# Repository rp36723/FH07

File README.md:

# FH07

A Monorepo for ECE364D Senior Design, team FH07

This repo is maintained with the meson build system.

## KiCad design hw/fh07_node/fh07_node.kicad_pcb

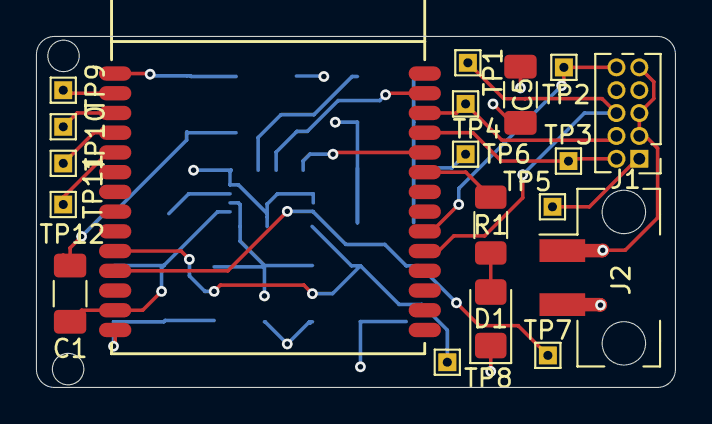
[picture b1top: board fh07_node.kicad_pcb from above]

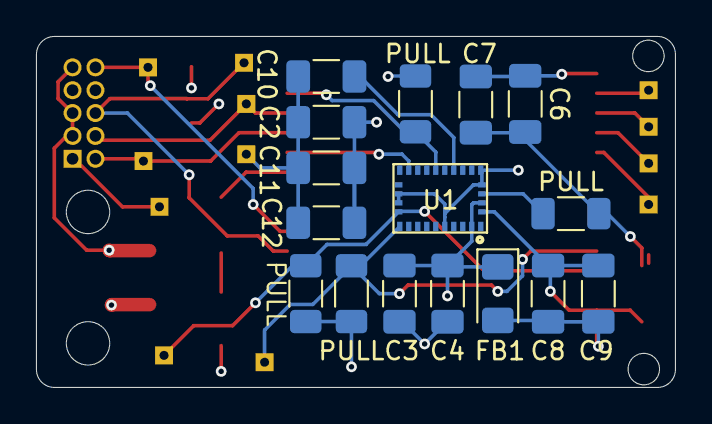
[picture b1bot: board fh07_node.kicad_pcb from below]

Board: 4 copper layers, 35.5 x 19.5 mm, 35 parts (16 on the bottom side), 19 nets.

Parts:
C1, C2, C3, C4, C5, C6, C7: C_Small; C_1206_3216Metric_Pad1.33x1.80mm_HandSolder
C8: 0.1 uF; C_1206_3216Metric_Pad1.33x1.80mm_HandSolder
C9: 4.7 uF; C_1206_3216Metric_Pad1.33x1.80mm_HandSolder
C10: 1 uF; C_1206_3216Metric_Pad1.33x1.80mm_HandSolder
C11: 120 nF; C_1206_3216Metric_Pad1.33x1.80mm_HandSolder
C12: 100 nF; C_1206_3216Metric_Pad1.33x1.80mm_HandSolder
D1: LED; D_1206_3216Metric_Pad1.42x1.75mm_HandSolder
FB1: FerriteBead; D_1206_3216Metric_Pad1.42x1.75mm_HandSolder
J1: Conn_ARM_JTAG_SWD_10; PinHeader_2x05_P1.27mm_Vertical
J2: Conn_01x02; Molex_Micro-Fit_3.0_43650-0221_1x02_P3.00mm_Vertical
M1: ME54BS01_V1.0
PULL: 4.7k; R_1206_3216Metric_Pad1.30x1.75mm_HandSolder
PULL#2, PULL#4: 10k; R_1206_3216Metric_Pad1.30x1.75mm_HandSolder
PULL#3: 4.7k; R_1206_3216Metric_Pad1.30x1.75mm_HandSolder
R1: 2.2 kΩ; R_1206_3216Metric_Pad1.30x1.75mm_HandSolder
TP1: TestPoint_SWO; TestPoint_THTPad_1.0x1.0mm_Drill0.5mm
TP2: TestPoint_nRESET; TestPoint_THTPad_1.0x1.0mm_Drill0.5mm
TP3: TestPoint_SWDIO; TestPoint_THTPad_1.0x1.0mm_Drill0.5mm
TP4: TestPoint_SWCLK; TestPoint_THTPad_1.0x1.0mm_Drill0.5mm
TP5: TestPoint_VCC; TestPoint_THTPad_1.0x1.0mm_Drill0.5mm
TP6: TestPoint_GND; TestPoint_THTPad_1.0x1.0mm_Drill0.5mm
TP7: TestPoint_SCL; TestPoint_THTPad_1.0x1.0mm_Drill0.5mm
TP8: TestPoint_SDA; TestPoint_THTPad_1.0x1.0mm_Drill0.5mm
TP9: TestPoint_1; TestPoint_THTPad_1.0x1.0mm_Drill0.5mm
TP10: TestPoint_2; TestPoint_THTPad_1.0x1.0mm_Drill0.5mm
TP11: TestPoint_3; TestPoint_THTPad_1.0x1.0mm_Drill0.5mm
TP12: TestPoint_4; TestPoint_THTPad_1.0x1.0mm_Drill0.5mm
U1: BNO055; LGA28R50P4X10_380X520X100

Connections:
+2V5: C1.1, C2.1, C3.1, C4.1, C5.1, C6.1, C7.1, C11.1, C12.1, FB1.1, J1.1 (VTref), J2.2, PULL.1, PULL#2.1, PULL#3.1, PULL#4.1, TP5.1, U1.3 (VDD), U1.28 (VDDIO)
/MCU/BNO_INT: M1.24 (P0.01), U1.14 (INT)
/MCU/BNO_nRESET: M1.27 (P0.02), PULL#2.2, U1.11 (NRESET)
/MCU/LED_STAT: M1.23 (P0.00), R1.1
/MCU/VCCM_nRF: C8.1, C9.1, FB1.2, M1.14 (VCCM_nRF)
/SCL: M1.11 (P1.03/NFC2), PULL#3.2, TP7.1, U1.19 (COM1)
/SDA: M1.10 (P1.02/NFC1), PULL.2, TP8.1, U1.20 (COM0)
/SWCLK: J1.4 (SWCLK/TCK), M1.26 (SWDCLK), TP4.1
/SWDIO: J1.2 (SWDIO/TMS), M1.25 (SWDIO), TP3.1
/SWO: J1.6 (SWO/TDO), M1.19 (P2.07), TP1.1
/Sensors/BNO_nBOOT_LOAD_PIN: PULL#4.2, U1.4 (NBOOT_LOAD_PIN)
/TP_1: M1.2 (P1.09), TP9.1
/TP_2: M1.3 (P1.10), TP10.1
/TP_3: M1.4 (P1.11/AIN4), TP11.1
/TP_4: M1.5 (P1.12/AIN5), TP12.1
/nRESET: J1.10 (~RESET), M1.20 (NRESET), TP2.1
GND: C1.2, C2.2, C3.2, C4.2, C5.2, C6.2, C7.2, C8.2, C9.2, C10.2, C11.2, C12.2, D1.1 (K), J1.3 (GND), J1.5 (GND), J1.9 (GNDDetect), J2.1, M1.1 (GND), M1.13 (GND), TP6.1, U1.2 (GND), U1.5 (PS1), U1.6 (PS0), U1.17 (COM3), U1.18 (COM2), U1.25 (GNDIO)
unnamed: D1.2 (A), R1.2
unnamed: C10.1, U1.9 (CAP)

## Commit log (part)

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2025-10-27 Basic init for messaging formats
2025-10-27 Added basic README
2025-10-27 Gitignore comments
2025-10-27 Added timestamp functionality
2025-10-27 Cleaned up build scripts and added flatbuffer dependency
2025-10-27 README updates
2025-11-13 risk reduction html page
2025-11-19 mockup for mobile app
2025-11-19 Add outlier_detection.html for individual risk-reduction activity
    This HTML file provides a user interface for analyzing posture sensor data, displaying statistics and identifying outliers based on simulated readings.
2025-11-19 Fix HTML formatting in outlier_detection.html
2025-11-19 Added node project
2026-01-28 Changed board devicetree file and added start of schematic
2026-01-28 Added ble lib outline
2026-01-28 Added CMake libs
2026-02-02 Got filestream of imu data working with TF-M partition
2026-02-03 Added windows only working mock bluetooth GATT server tool
2026-02-04 Inited basic hardware schematic
2026-02-07 Add ME54BS01 power filtering and decoupling
    - Added ferrite bead between VCC and VCCM_nRF
    - Added 0.1uF + 4.7uF decoupling on module supply
    - Confirmed SWD connectivity and GPIO availability
2026-02-07 Add IMU and magnetometer schematics and libraries
    - Added ICM-42670-P IMU schematic
    - Added BMM350 magnetometer schematic
    - Added symbols, footprints, and 3D models to repo libraries
2026-02-09 Mock Sensor Data
2026-02-24 Pushed updates to hardware
    Completed sensors.kicad_sch
    Added BNO055 symbol and footprint files to Part_Libraries
    Added I²C pull-ups, reset circuitry, and required decoupling components
    Followed the BNO055 connection diagram from the datasheet for wiring
2026-02-25 Updated sensor node and top level sheet
    Fixed pin naming on sensor module and update MCU and Sensor top sheet
2026-03-02 New KiCad version test
2026-03-02 Added gitignore for kicad backups
2026-03-02 Added newline
2026-03-02 Cleaning up old .zip files
    Cleaned up the file tree
2026-03-02 BNO055 Footprint
2026-03-03 Completed hardware revision 1 release
2026-03-04 Update version
2026-03-04 Added rounded corners
2026-03-04 Added holes
2026-03-04 Added basics of BLE lib
2026-04-07 Inited esp proj
2026-04-08 Updated rust code
2026-04-08 Init mobile app
2026-04-08 Slight tweaks
2026-04-08 Created basic app
2026-04-08 More patches
2026-04-08 Working mobile app
2026-04-08 Added diagnostics
2026-04-08 Refactor of the kotlin code to make future changes easier
2026-04-08 Cleaned up code and put it into seperate dirs for what each part does
2026-04-08 Added unit tests for the transmission protocol
2026-04-08 Switched to a ViewModel
2026-04-08 Added details and status updates to UI
2026-04-08 Added ability to save data
2026-04-08 Updated to allow for export of data
2026-04-08 Configured to setup for doing analysis
2026-04-08 Added analysis framework
2026-04-08 Added analysis for sitting
2026-04-08 Added seperate pages
2026-04-08 Added real imus
2026-04-08 Tweaked logged messages
2026-04-08 Added signed apk and updated loop times of firmware
2026-04-11 Added slight modeling ability (is bad)
2026-04-22 Added graph over time
2026-04-23 Bumped version down
2026-04-23 Added new apk
